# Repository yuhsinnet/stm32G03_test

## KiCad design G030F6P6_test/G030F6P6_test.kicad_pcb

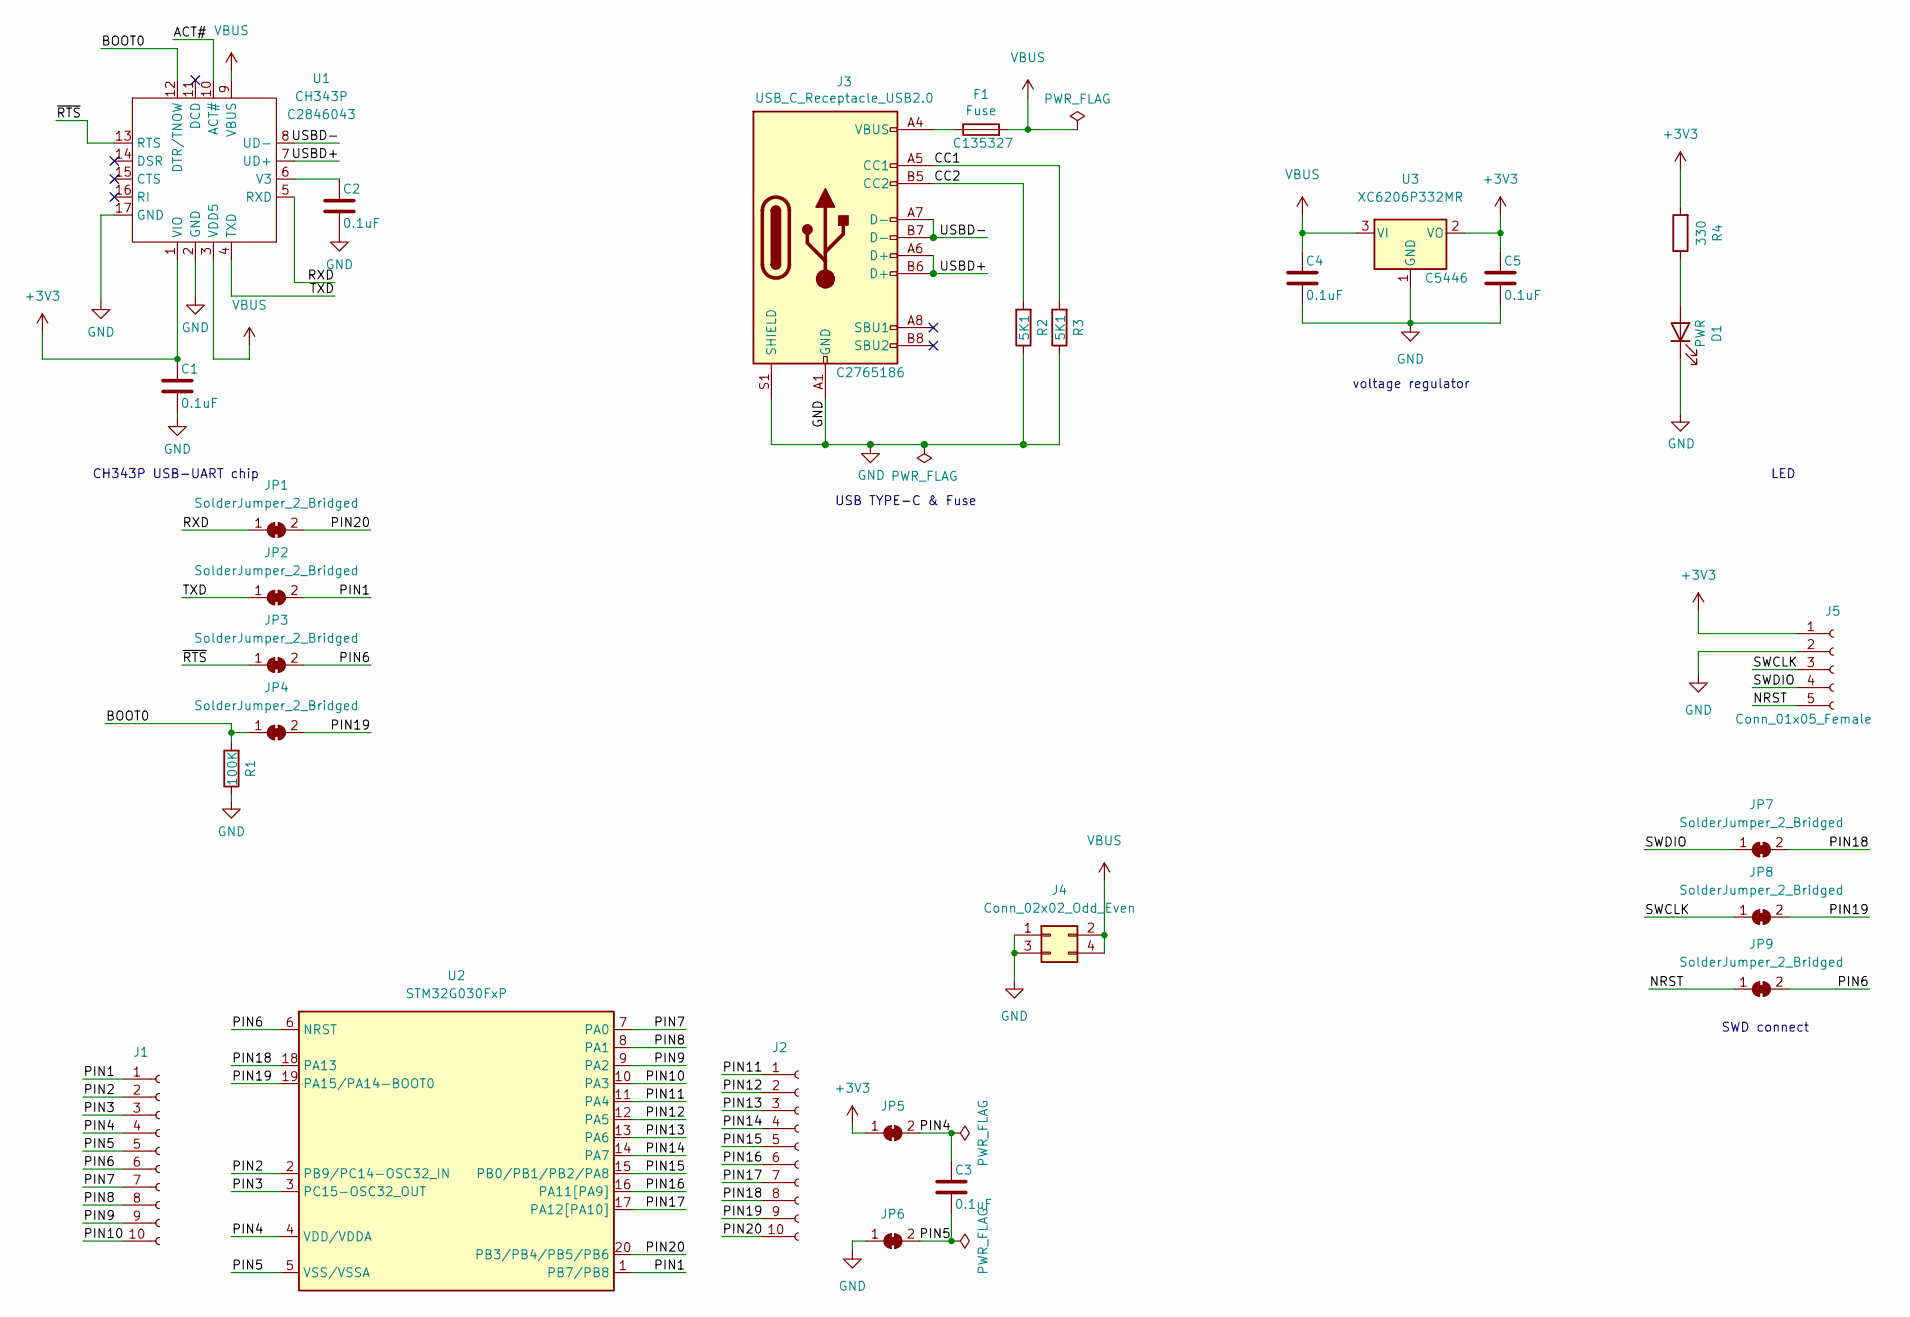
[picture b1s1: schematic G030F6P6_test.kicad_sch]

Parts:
C1, C2, C3, C4, C5: 0.1uF; C_0805_2012Metric; LCSC C72038
D1: PWR; LED_0805_2012Metric; LCSC C72038
F1: Fuse; Fuse_0805_2012Metric; LCSC C135327
J1, J2: Conn_01x10_Female; PinHeader_1x10_P2.54mm_Vertical
J3: USB_C_Receptacle_USB2.0; USB_C_Receptacle_HRO_TYPE-C-31-M-12; LCSC C2765186
J4: Conn_02x02_Odd_Even; PinSocket_2x02_P2.54mm_Vertical
J5: Conn_01x05_Female; PinHeader_1x05_P2.54mm_Vertical
JP1, JP2, JP3, JP4, JP5, JP6, JP7, JP8, JP9: SolderJumper_2_Bridged; SolderJumper-2_P1.3mm_Bridged2Bar_RoundedPad1.0x1.5mm
R1: 100K; R_0805_2012Metric; LCSC C149504
R2, R3: 5K1; R_0805_2012Metric; LCSC C27834
R4: 330; R_0805_2012Metric; LCSC C17630
U1: CH343P; QFN-16-1EP_3x3mm_P0.5mm_EP1.45x1.45mm_ThermalVias; LCSC C2846043
U2: STM32G030FxP; TSSOP-20_4.4x6.5mm_P0.65mm; LCSC C529330
U3: XC6206P332MR; SOT-23; LCSC C5446

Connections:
+3V3: C1.1, C5.1, J5.1, JP5.1 (A), R4.2, U1.1 (VIO), U3.2 (VO)
/ACT#: U1.10 (ACT#)
/BOOT0: JP4.1 (A), R1.2, U1.12 (DTR/TNOW)
/CC1: J3.A5 (CC1), R3.2
/CC2: J3.B5 (CC2), R2.2
/NRST: J5.5, JP9.1 (A)
/PIN1: J1.1, JP2.2 (B), U2.1 (PB7/PB8)
/PIN2: J1.2, U2.2 (PB9/PC14-OSC32_IN)
/PIN3: J1.3, U2.3 (PC15-OSC32_OUT)
/PIN4: C3.1, J1.4, JP5.2 (B), U2.4 (VDD/VDDA)
/PIN5: C3.2, J1.5, JP6.2 (B), U2.5 (VSS/VSSA)
/PIN6: J1.6, JP3.2 (B), JP9.2 (B), U2.6 (NRST)
/PIN7: J1.7, U2.7 (PA0)
/PIN8: J1.8, U2.8 (PA1)
/PIN9: J1.9, U2.9 (PA2)
/PIN10: J1.10, U2.10 (PA3)
/PIN11: J2.1, U2.11 (PA4)
/PIN12: J2.2, U2.12 (PA5)
/PIN13: J2.3, U2.13 (PA6)
/PIN14: J2.4, U2.14 (PA7)
/PIN15: J2.5, U2.15 (PB0/PB1/PB2/PA8)
/PIN16: J2.6, U2.16 (PA11[PA9])
/PIN17: J2.7, U2.17 (PA12[PA10])
/PIN18: J2.8, JP7.2 (B), U2.18 (PA13)
/PIN19: J2.9, JP4.2 (B), JP8.2 (B), U2.19 (PA15/PA14-BOOT0)
/PIN20: J2.10, JP1.2 (B), U2.20 (PB3/PB4/PB5/PB6)
/RXD: JP1.1 (A), U1.5 (RXD)
/SWCLK: J5.3, JP8.1 (A)
/SWDIO: J5.4, JP7.1 (A)
/TXD: JP2.1 (A), U1.4 (TXD)
/USBD+: J3.A6 (D+), J3.B6 (D+), U1.7 (UD+)
/USBD-: J3.A7 (D-), J3.B7 (D-), U1.8 (UD-)
/~RTS: JP3.1 (A), U1.13 (RTS)
GND: C1.2, C2.2, C4.2, C5.2, D1.1 (K), J3.A1 (GND), J3.A12 (GND), J3.B1 (GND), J3.B12 (GND), J3.S1 (SHIELD), J4.1, J4.3, J5.2, JP6.1 (A), R1.1, R2.1, R3.1, U1.2 (GND), U1.17 (GND), U3.1 (GND)
unnamed: C2.1, U1.6 (V3)
unnamed: D1.2 (A), R4.1
unnamed: F1.1, J3.A4 (VBUS), J3.A9 (VBUS), J3.B4 (VBUS), J3.B9 (VBUS)
VBUS: C4.1, F1.2, J4.2, J4.4, U1.3 (VDD5), U1.9 (VBUS), U3.3 (VI)

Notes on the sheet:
voltage regulator
CH343P USB-UART chip
SWD connect
USB TYPE-C & Fuse
LED

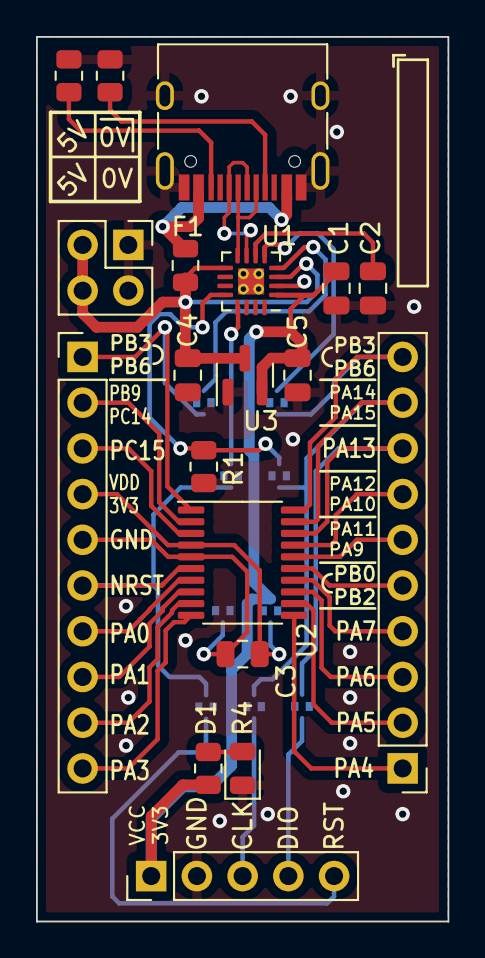
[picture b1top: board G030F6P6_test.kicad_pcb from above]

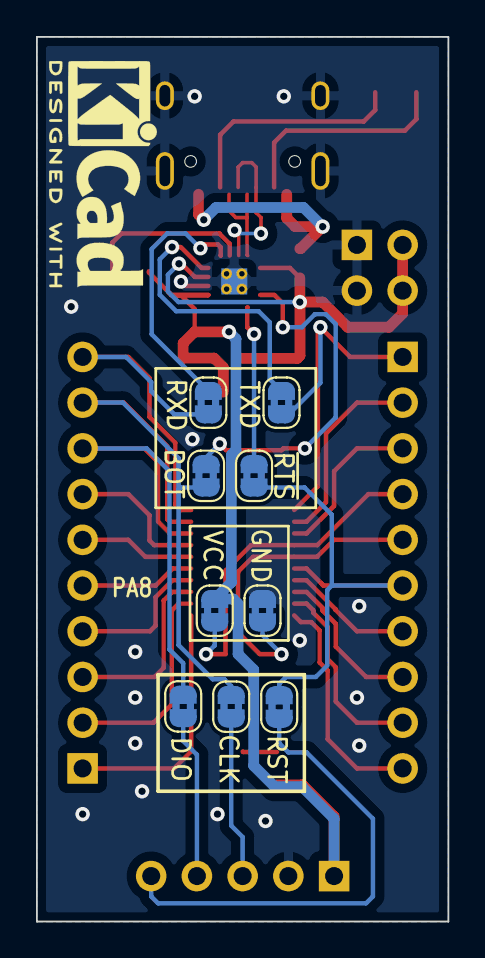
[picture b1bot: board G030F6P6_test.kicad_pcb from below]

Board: 2 copper layers, 22.9 x 49.1 mm, 28 parts (9 on the bottom side), 37 nets.

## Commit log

2022-06-03 add project
2022-06-03 add cpu
2022-06-04 add pab
2022-06-04 add 元件
2022-06-05 Update G030F6P6_test.kicad_sch
    移除jump 的 BOM 標記
    新增CH343P 元件
    連結各對外腳位(SWD、UART、BOOT0)
2022-06-05 Update G030F6P6_test.kicad_sch
    增加 VBUS、外部電源選擇接腳
    執行電器檢查正常規則調整
2022-06-05 Update G030F6P6_test.kicad_sch
    fix STM32 電源誤用5V
    CH343P 調整位置
2022-06-05 Update G030F6P6_test.kicad_sch
    更新指示燈名稱
    新增CPU 濾波電容
2022-06-06 Update G030F6P6_test.kicad_sch
    增加 LCSC 編號
2022-06-06 Update G030F6P6_test.kicad_sch
    更新CH343P 符號
2022-06-06 Update G030F6P6_test.kicad_sch
    修改 JP2 封裝
2022-06-06 Update G030F6P6_test.kicad_pcb
    元件初次放置
2022-06-06 Update G030F6P6_test.kicad_sch
    移除LED
    更換 CH343P 封裝
2022-06-06 PCB 板放置零件
2022-06-07 Update G030F6P6_test.kicad_sch
    移除電壓選擇
2022-06-07 Update G030F6P6_test.kicad_sch
    交換 SWCLK 與 SWDIO
2022-06-07 布局完成
2022-06-08 調整腳位位置
2022-06-11 Update G030F6P6_test.kicad_sch
    增加 5V 連接腳位
2022-06-11 調整細節
    增加 5V 腳位封裝
    調整部分位置
2022-06-11 add jlcpcb
2022-06-11 調整線路位置
2022-06-11 送交打樣
2022-06-12 jlcpcb 打樣
2023-04-23 軟體升級KiCAD V7
